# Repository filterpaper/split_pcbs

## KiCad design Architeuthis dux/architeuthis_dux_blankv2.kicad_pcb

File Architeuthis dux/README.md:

# Simplified Architeuthis dux

Simplified versions of [tapioki](https://github.com/tapioki)'s [Architeuthis dux](https://github.com/tapioki/cephalopoda/tree/main/Architeuthis%20dux) with hotswap socket and puck support removed, fixed phantom drill holes

## Instructions
To build an Architeuthis dux, you need the following:
* 2 [pro-micro](https://www.aliexpress.com/item/32971098005.html) controllers ([Elite-C](https://boardsource.xyz/store/5ef67ea66786dc1e65a80708) or [Pro-micro C](https://www.aliexpress.com/item/1005003230811462.html))
* 2 [PJ320A](https://www.aliexpress.com/item/1005001928651798.html) audio jack
* 1 male-to-male [TRRS](https://www.aliexpress.com/item/32961128759.html) cable
* 34 [Kailh choc v1](https://www.aliexpress.com/item/4000907409650.html) switches and [keycaps](https://boardsource.xyz/store/5f6ef2d68e3bf05ab838f918)
* Rubber feet or bumbers for the bottom
* Optional: [low profile socket](https://www.digikey.com/product-detail/en/315-43-112-41-003000/ED4764-12-ND/4455232) with [Mill-max pins](https://www.digikey.com/product-detail/en/3320-0-00-15-00-00-03-0/ED1134-ND/4147392), or [budget socket pins](https://www.aliexpress.com/item/32852480645.html) with [round pin headers](https://www.aliexpress.com/item/32692992041.html)

Note: Architeuthis dux is a double sided PCB so controllers face down on the left and face up on the right.

## QMK Firmware
To build the QMK firmware, run:
```
qmk compile -kb a_dux -km default
```

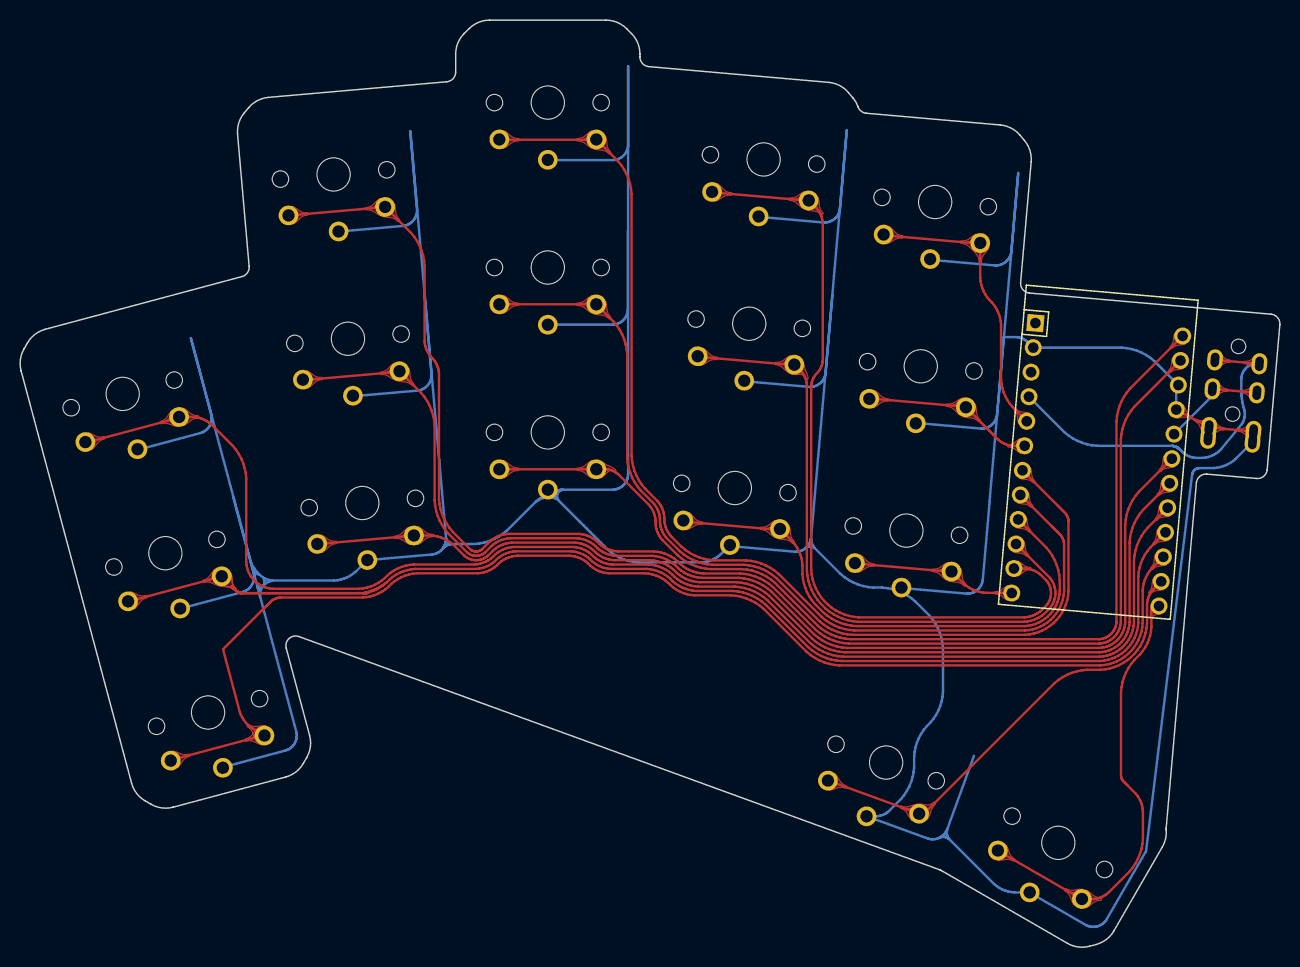
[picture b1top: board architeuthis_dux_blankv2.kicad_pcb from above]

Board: 2 copper layers, 129.9 x 95.6 mm, 19 parts (0 on the bottom side), 20 nets.

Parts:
C1: ProMicro
S2, S4, S6, S8, S10, S12, S14, S16, S18, S20, S22, S24, S26, S28, S30, S32, S34: PG1350
T1: TRRS-PJ-320A-dual

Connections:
GND: C1.2, C1.15, C1.16, S2.2, S4.2, S6.2, S8.2, S10.2, S12.2, S14.2, S16.2, S18.2, S20.2, S22.2, S24.2, S26.2, S28.2, S30.2, S32.2, S34.2, T1.1, T1.2
P0: C1.14, S12.1
P1: C1.13, S14.1
P2: C1.17, T1.3
P3: C1.18, S10.1
P4: C1.19, S8.1
P5: C1.20, S6.1
P6: C1.21, S4.1
P7: C1.22, S2.1
P8: C1.23, S32.1
P9: C1.24, S34.1
P10: C1.12, S26.1
P14: C1.10, S22.1
P15: C1.9, S20.1
P16: C1.11, S24.1
P18: C1.8, S18.1
P19: C1.7, S16.1
P20: C1.6, S28.1
P21: C1.5, S30.1
VCC: C1.4, T1.4

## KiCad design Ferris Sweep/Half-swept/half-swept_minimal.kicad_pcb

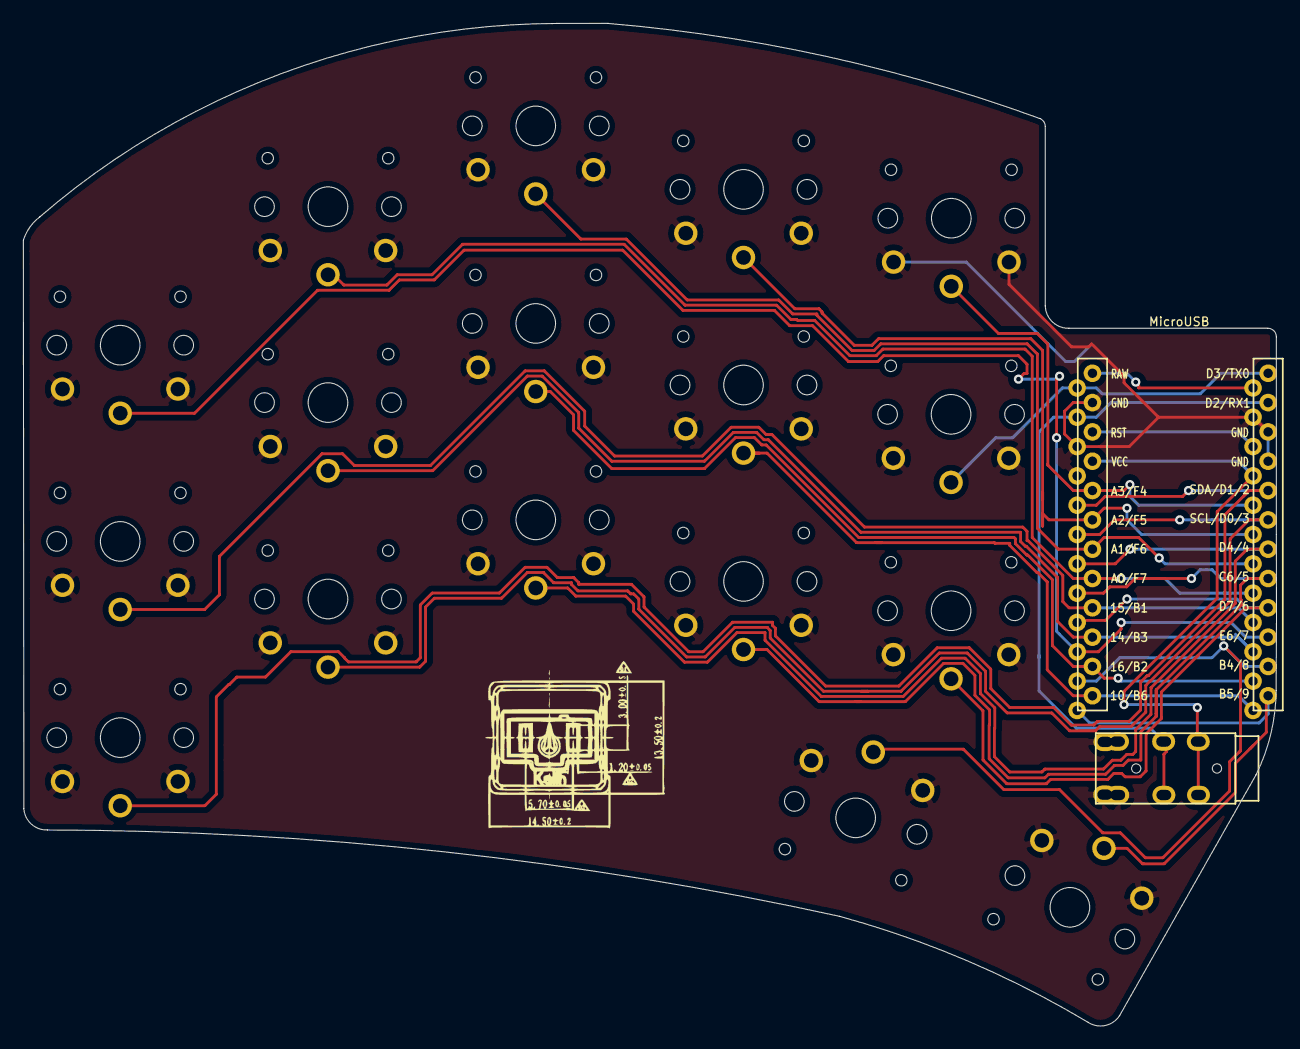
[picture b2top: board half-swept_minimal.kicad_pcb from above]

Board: 2 copper layers, 108.6 x 86.9 mm, 19 parts (0 on the bottom side), 20 nets.

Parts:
J2: AudioJack4dpb; TRRS-PJ-DPB2
SW2, SW3, SW4, SW5, SW6, SW8, SW9, SW10, SW11, SW12, SW14, SW15, SW16, SW17, SW18, SW20, SW21: SW_Push; SW_PG1350_rev_DPB
U1: ProMicro-kbd; ProMicro_v2

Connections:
Switch1: SW2.1, U1.10
Switch2: SW3.1, U1.17
Switch3: SW4.1, U1.18
Switch4: SW5.1, U1.19
Switch5: SW6.1, U1.20
Switch6: SW8.1, U1.16
Switch7: SW9.1, U1.15
Switch8: SW10.1, U1.14
Switch9: SW11.1, U1.13
Switch10: SW12.1, U1.1
Switch11: SW14.1, U1.5
Switch12: SW15.1, U1.6
Switch13: SW16.1, U1.7
Switch14: SW17.1, U1.8
Switch15: SW18.1, U1.9
Switch16: SW21.1, U1.11
Switch17: SW20.1, U1.12
Switch18: J2.R1, U1.2
gnd: J2.S, J2.T, SW2.2, SW3.2, SW4.2, SW5.2, SW6.2, SW8.2, SW9.2, SW10.2, SW11.2, SW12.2, SW14.2, SW15.2, SW16.2, SW17.2, SW18.2, SW20.2, SW21.2, U1.3, U1.4, U1.23
vcc: J2.R2, U1.21
